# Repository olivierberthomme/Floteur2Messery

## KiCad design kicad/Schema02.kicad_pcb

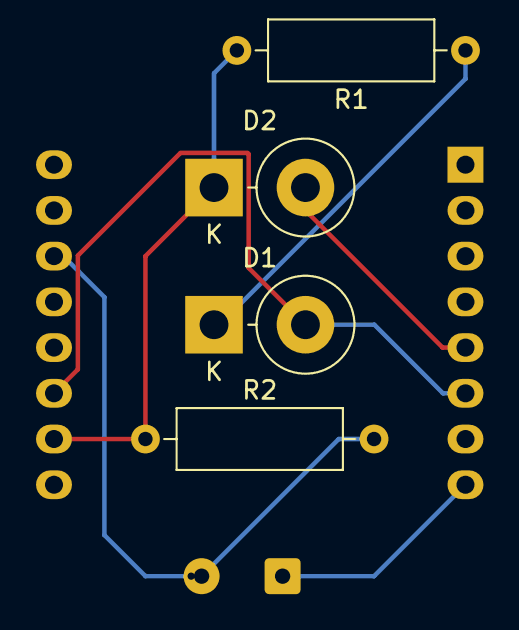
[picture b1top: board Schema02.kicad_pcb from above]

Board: 2 copper layers, 6 parts (0 on the bottom side), 6 nets.

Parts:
D1: LED Bleue; D_DO-201AD_P5.08mm_Vertical_KathodeUp
D2: LED Rouge; D_DO-201AD_P5.08mm_Vertical_KathodeUp
J1: Conn_01x02; SolderWire-0.25sqmm_1x02_P4.5mm_D0.65mm_OD2mm
R1, R2: R; R_Axial_DIN0309_L9.0mm_D3.2mm_P12.70mm_Horizontal
U1: WeMos_D1_mini; WEMOS_D1_mini_light

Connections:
unnamed: D1.1, R1.1
unnamed: D1.2, U1.6, U1.11
unnamed: D2.1, R1.2, R2.1, U1.10
unnamed: D2.2, U1.5
unnamed: J1.1, U1.8
unnamed: J1.2, R2.2, U1.14

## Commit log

2020-09-27 Public
2020-09-27 Create LICENSE
2020-09-27 Moved to secrets.h
2020-11-22 Added retry if internet fails
2021-11-28 Do not send message by night and 1 message/day if all good
2023-12-18 Add birthday message
